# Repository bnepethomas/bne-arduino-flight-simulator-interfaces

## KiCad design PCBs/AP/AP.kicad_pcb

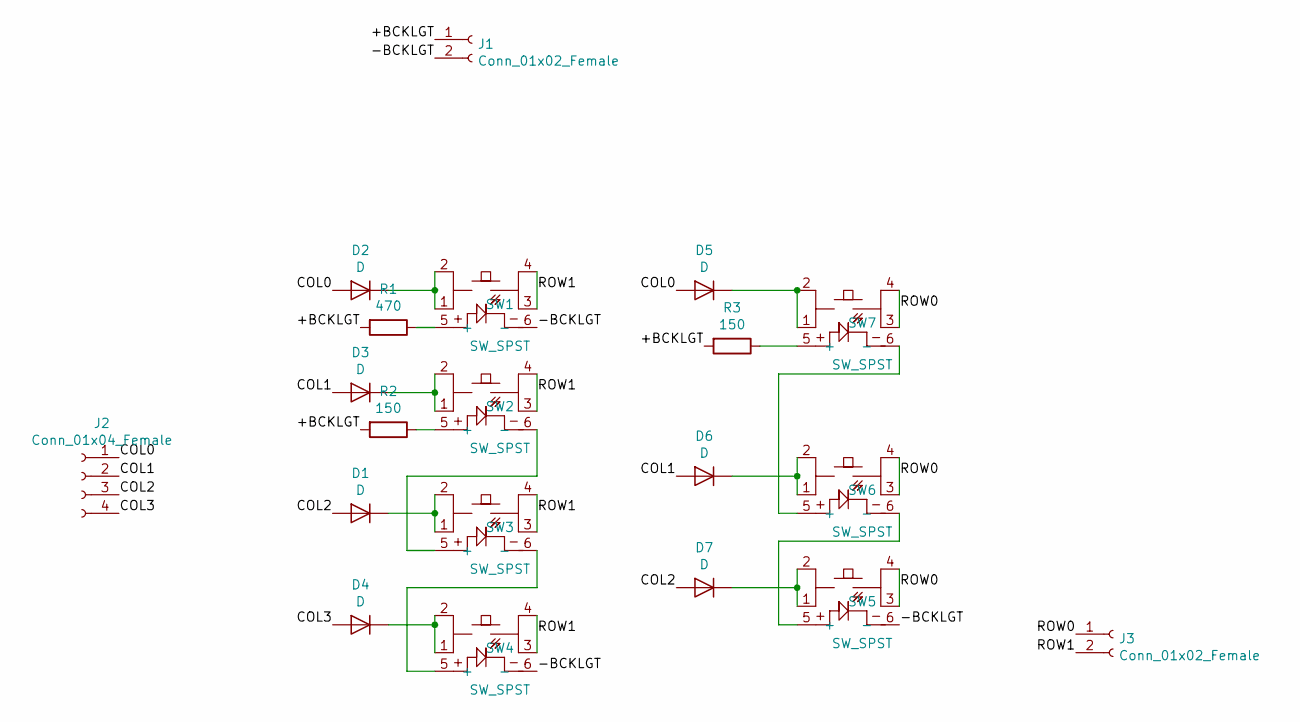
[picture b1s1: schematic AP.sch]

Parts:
D1, D2, D3, D4, D5, D6, D7: D; D_Signal_P7.62mm_Horizontal
J1, J3: Conn_01x02_Female; PinSocket_1x02_P2.54mm_Vertical
J2: Conn_01x04_Female; PinHeader_1x04_P2.54mm_Vertical
R1: 470; R_Axial_DIN0207_L6.3mm_D2.5mm_P7.62mm_Horizontal
R2, R3: 150; R_Axial_DIN0207_L6.3mm_D2.5mm_P7.62mm_Horizontal
SW1, SW2, SW3, SW4, SW5, SW6, SW7: SW_SPST; PT_Small_Tactile_Switch_With_LED

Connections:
/+BCKLGT: J1.1, R1.2, R2.2, R3.2
/-BCKLGT: J1.2, SW1.6 (-), SW4.6 (-), SW5.6 (-)
/COL0: D2.2 (A), D5.2 (A), J2.1
/COL1: D3.2 (A), D6.2 (A), J2.2
/COL2: D1.2 (A), D7.2 (A), J2.3
/COL3: D4.2 (A), J2.4
/ROW0: J3.1, SW5.3, SW5.4, SW6.3, SW6.4, SW7.3, SW7.4
/ROW1: J3.2, SW1.3, SW1.4, SW2.3, SW2.4, SW3.3, SW3.4, SW4.3, SW4.4
unnamed: D1.1 (K), SW3.1, SW3.2
unnamed: D2.1 (K), SW1.1, SW1.2
unnamed: D3.1 (K), SW2.1, SW2.2
unnamed: D4.1 (K), SW4.1, SW4.2
unnamed: D5.1 (K), SW7.1, SW7.2
unnamed: D6.1 (K), SW6.1, SW6.2
unnamed: D7.1 (K), SW5.1, SW5.2
unnamed: R1.1, SW1.5 (+)
unnamed: R2.1, SW2.5 (+)
unnamed: R3.1, SW7.5 (+)
unnamed: SW2.6 (-), SW3.5 (+)
unnamed: SW3.6 (-), SW4.5 (+)
unnamed: SW5.5 (+), SW6.6 (-)
unnamed: SW6.5 (+), SW7.6 (-)

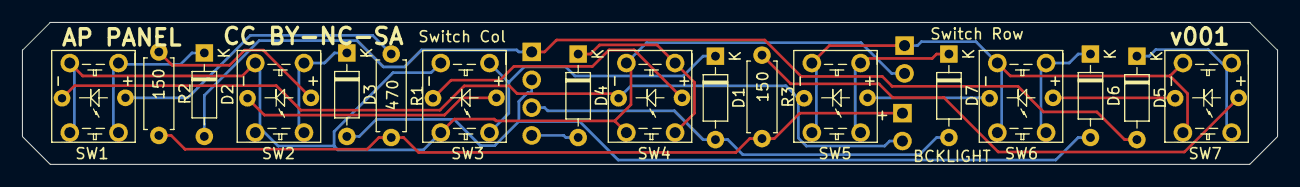
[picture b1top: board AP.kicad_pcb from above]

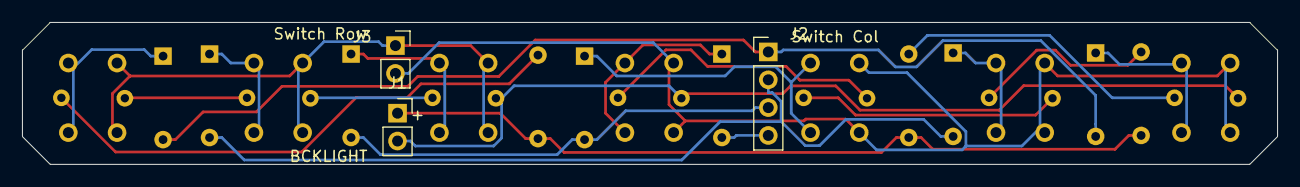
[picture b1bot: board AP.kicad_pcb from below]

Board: 2 copper layers, 114.6 x 13.0 mm, 20 parts (3 on the bottom side), 22 nets.

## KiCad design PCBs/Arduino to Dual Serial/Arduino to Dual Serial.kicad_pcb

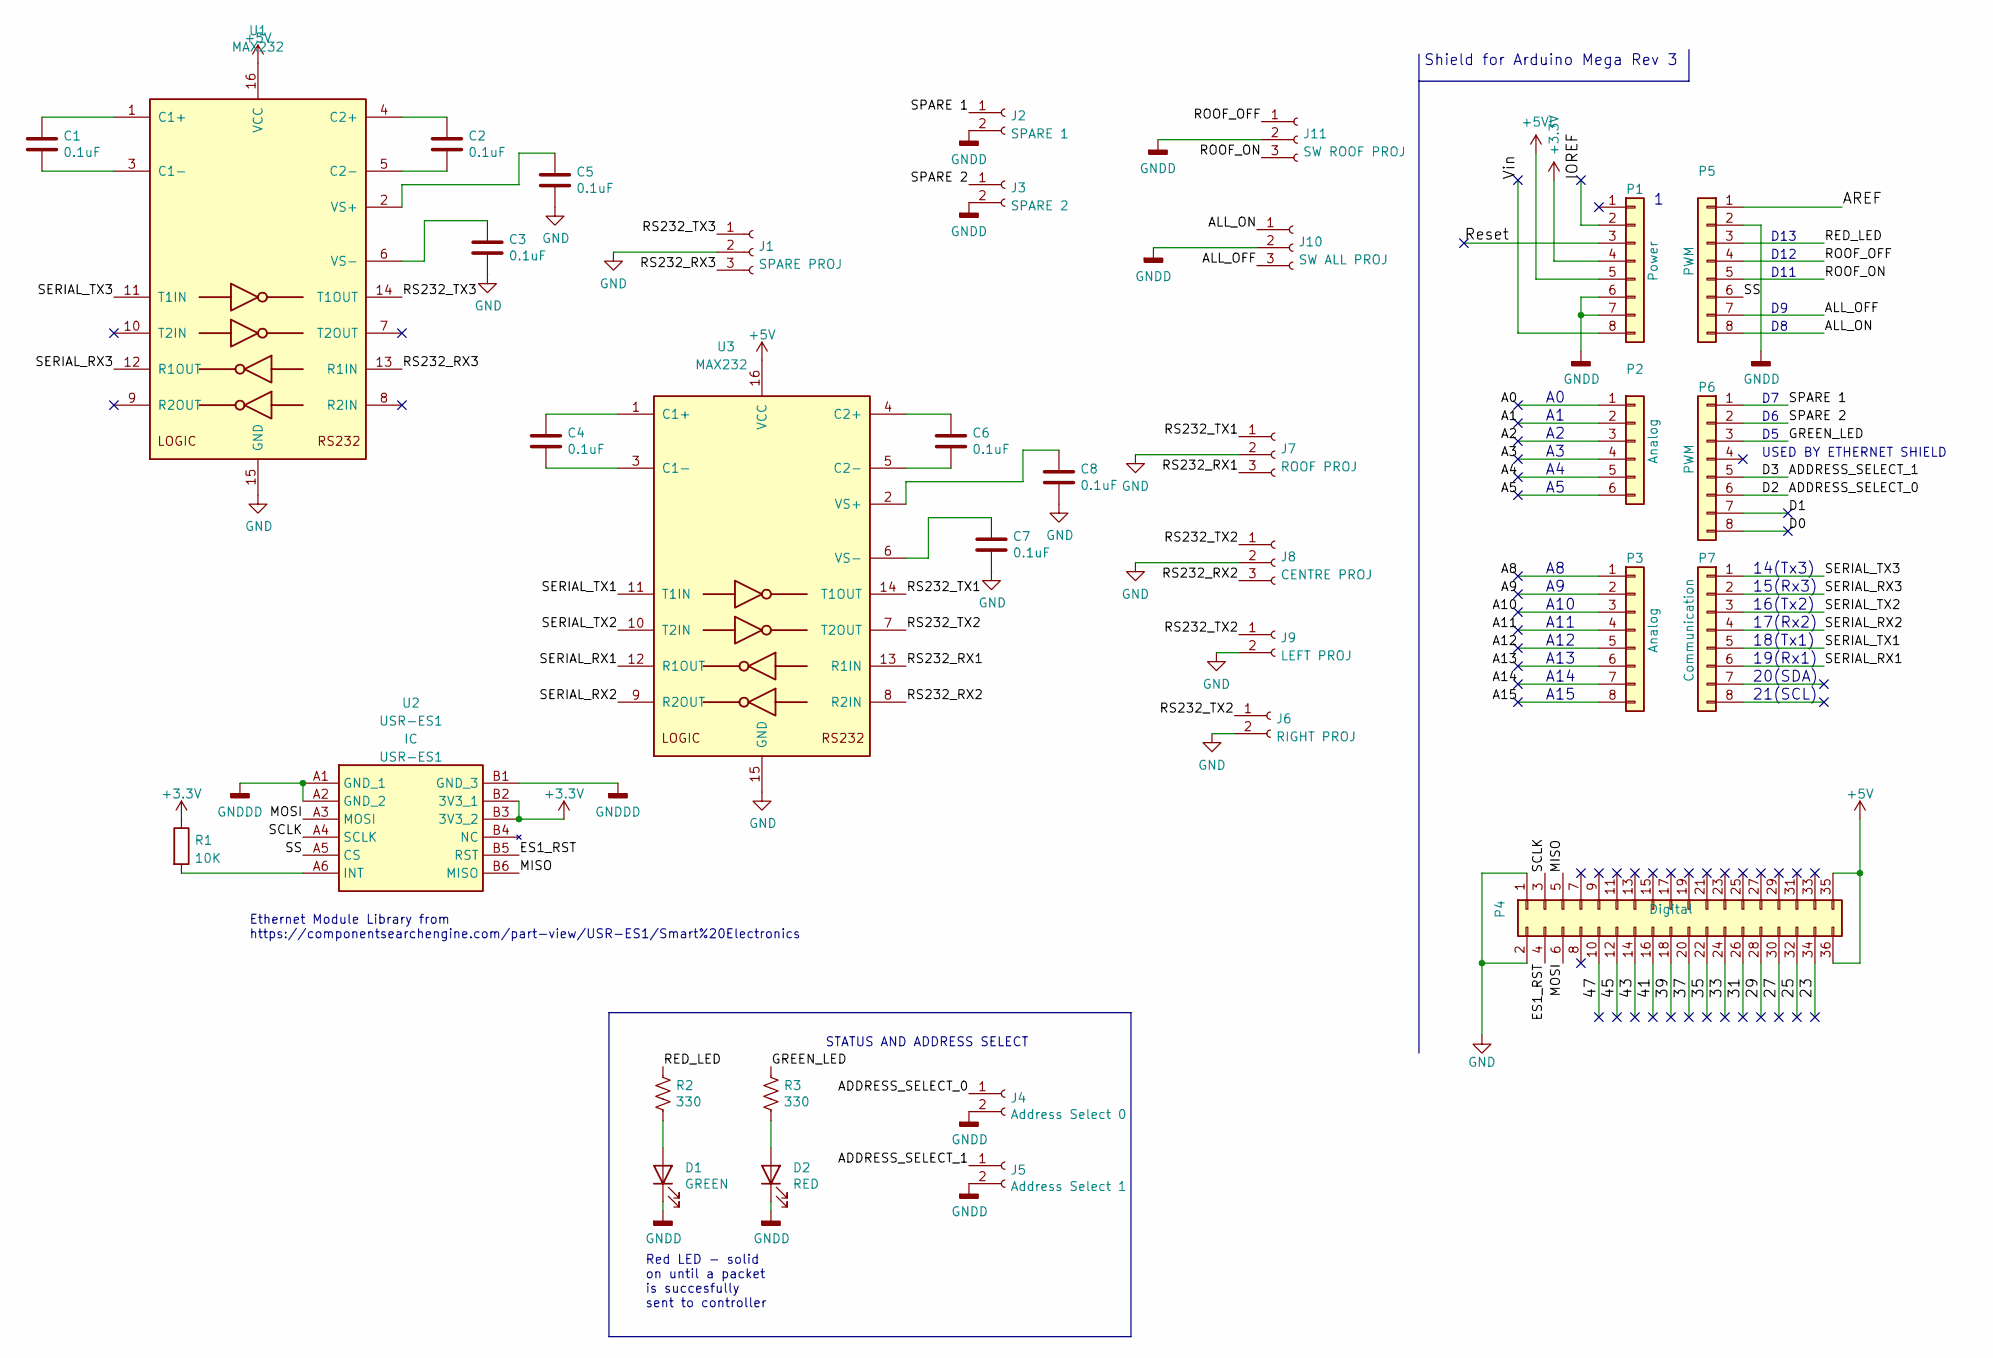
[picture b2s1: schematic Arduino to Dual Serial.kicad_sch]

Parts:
C1, C2, C3, C4, C5, C6, C7, C8: 0.1uF; C_Disc_D4.3mm_W1.9mm_P5.00mm
D1: GREEN; LED_D3.0mm
D2: RED; LED_D3.0mm
J1: SPARE PROJ; Molex_KK-254_AE-6410-03A_1x03_P2.54mm_Vertical
J2: SPARE 1; Molex_KK-254_AE-6410-02A_1x02_P2.54mm_Vertical
J3: SPARE 2; Molex_KK-254_AE-6410-02A_1x02_P2.54mm_Vertical
J4: Address Select 0; PinHeader_1x02_P2.54mm_Vertical
J5: Address Select 1; PinHeader_1x02_P2.54mm_Vertical
J6: RIGHT PROJ; Molex_KK-254_AE-6410-02A_1x02_P2.54mm_Vertical
J7: ROOF PROJ; Molex_KK-254_AE-6410-03A_1x03_P2.54mm_Vertical
J8: CENTRE PROJ; Molex_KK-254_AE-6410-03A_1x03_P2.54mm_Vertical
J9: LEFT PROJ; Molex_KK-254_AE-6410-02A_1x02_P2.54mm_Vertical
J10: SW ALL PROJ; Molex_KK-254_AE-6410-03A_1x03_P2.54mm_Vertical
J11: SW ROOF PROJ; Molex_KK-254_AE-6410-03A_1x03_P2.54mm_Vertical
P1: Power; Socket_Strip_Arduino_1x08
P2: Analog; PinHeader_1x06_P2.54mm_Vertical
P3: Analog; Socket_Strip_Arduino_1x08
P4: Digital; Socket_Strip_Arduino_2x18
P5: PWM; PinHeader_1x08_P2.54mm_Vertical
P6: PWM; Socket_Strip_Arduino_1x08
P7: Communication; Socket_Strip_Arduino_1x08
R1: 10K; PT_R_Axial_DIN0204_L3.6mm_D1.6mm_P2.54mm_Vertical
R2, R3: 330; PT_R_Axial_DIN0204_L3.6mm_D1.6mm_P2.54mm_Vertical
U1, U3: MAX232; DIP-16_W7.62mm
U2: USR-ES1; USRES1; Manufacturer_Part_Number USR-ES1

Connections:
+3.3V: P1.4, R1.1, U2.B2 (3V3_1), U2.B3 (3V3_2)
+5V: P4.35, P4.36, U1.16 (VCC), U3.16 (VCC)
+5VL: P1.5
/23: P4.34
/25: P4.32
/27: P4.30
/29: P4.28
/31: P4.26
/33: P4.24
/35: P4.22
/37: P4.20
/39: P4.18
/41: P4.16
/43: P4.14
/45: P4.12
/47: P4.10
/A0: P2.1
/A1: P2.2
/A2: P2.3
/A3: P2.4
/A4: P2.5
/A5: P2.6
/A8: P3.1
/A9: P3.2
/A10: P3.3
/A11: P3.4
/A12: P3.5
/A13: P3.6
/A14: P3.7
/A15: P3.8
/ADDRESS_SELECT_0: J4.1, P6.6
/ADDRESS_SELECT_1: J5.1, P6.5
/ALL_OFF: J10.3, P5.7
/ALL_ON: J10.1, P5.8
/AREF: P5.1
/D0: P6.8
/D1: P6.7
/ES1_RST: P4.4, U2.B5 (RST)
/GREEN_LED: P6.3, R3.1
/IOREF: P1.2
/MISO: P4.5, U2.B6 (MISO)
/MOSI: P4.6, U2.A3 (MOSI)
/RED_LED: P5.3, R2.1
/ROOF_OFF: J11.1, P5.4
/ROOF_ON: J11.3, P5.5
/RS232_RX1: J7.3, U3.13 (R1IN)
/RS232_RX2: J8.3, U3.8 (R2IN)
/RS232_RX3: J1.3, U1.13 (R1IN)
/RS232_TX1: J7.1, U3.14 (T1OUT)
/RS232_TX2: J6.1, J8.1, J9.1, U3.7 (T2OUT)
/RS232_TX3: J1.1, U1.14 (T1OUT)
/Reset: P1.3
/SCLK: P4.3, U2.A4 (SCLK)
/SERIAL_RX1: P7.6, U3.12 (R1OUT)
/SERIAL_RX2: P7.4, U3.9 (R2OUT)
/SERIAL_RX3: P7.2, U1.12 (R1OUT)
/SERIAL_TX1: P7.5, U3.11 (T1IN)
/SERIAL_TX2: P7.3, U3.10 (T2IN)
/SERIAL_TX3: P7.1, U1.11 (T1IN)
/SPARE 1: J2.1, P6.1
/SPARE 2: J3.1, P6.2
/SS: P5.6, U2.A5 (CS)
/Vin: P1.8
GND: C3.2, C5.2, C7.2, C8.2, J1.2, J6.2, J7.2, J8.2, J9.2, P4.1, P4.2, U1.15 (GND), U3.15 (GND)
unnamed: C1.1, U1.1 (C1+)
unnamed: C1.2, U1.3 (C1-)
unnamed: C2.1, U1.4 (C2+)
unnamed: C2.2, U1.5 (C2-)
unnamed: C3.1, U1.6 (VS-)
unnamed: C4.1, U3.1 (C1+)
unnamed: C4.2, U3.3 (C1-)
unnamed: C5.1, U1.2 (VS+)
unnamed: C6.1, U3.4 (C2+)
unnamed: C6.2, U3.5 (C2-)
unnamed: C7.1, U3.6 (VS-)
unnamed: C8.1, U3.2 (VS+)
unnamed: D1.2 (A), R2.2
unnamed: D2.2 (A), R3.2
unnamed: R1.2, U2.A6 (INT)

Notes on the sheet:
A10
14(Tx3)
21(SCL)
USED BY ETHERNET SHIELD
20(SDA)
A15
A13
17(Rx2)
D12
A11
D13
16(Tx2)
Red LED - solid on until a packet is succesfully sent to controller
18(Tx1)
19(Rx1)
15(Rx3)
D11
Shield for Arduino Mega Rev 3
A14
Ethernet Module Library from https://componentsearchengine.com/part-view/USR-ES1/Smart%20Electronics
STATUS AND ADDRESS SELECT
A12

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
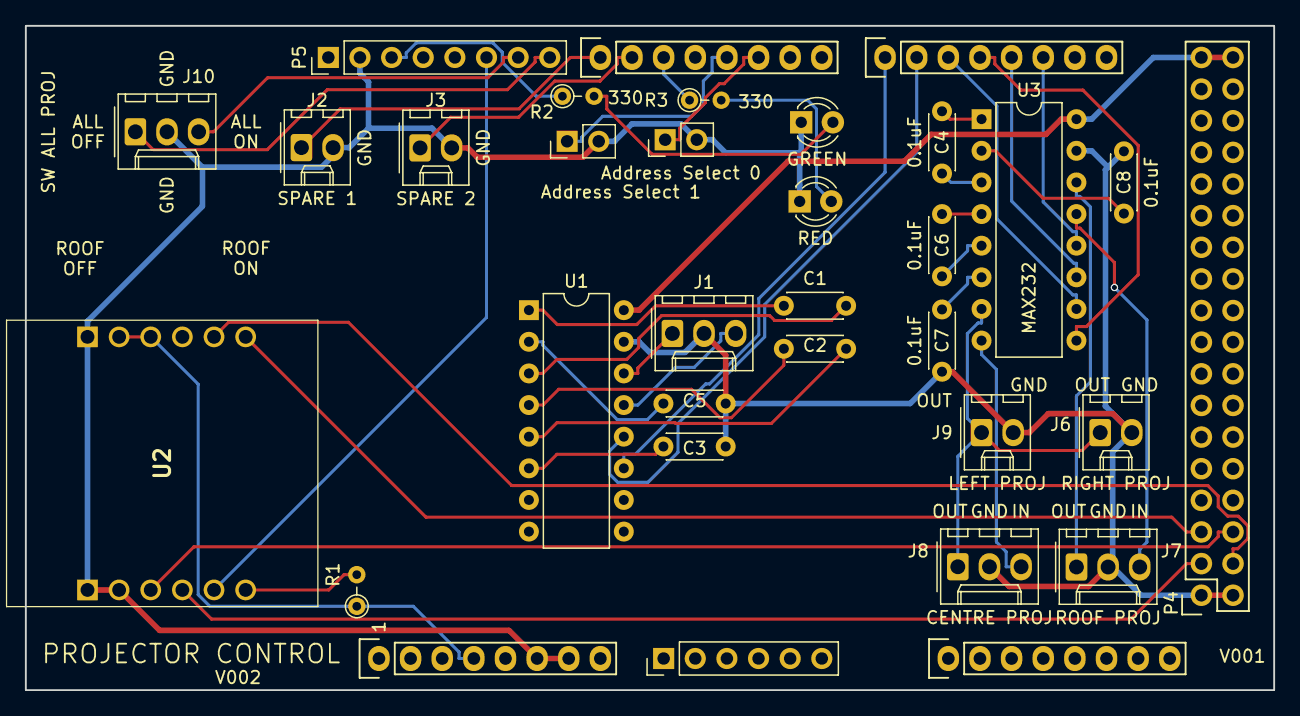
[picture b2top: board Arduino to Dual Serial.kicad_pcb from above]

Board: 2 copper layers, 100.2 x 53.3 mm, 33 parts (0 on the bottom side), 44 nets.

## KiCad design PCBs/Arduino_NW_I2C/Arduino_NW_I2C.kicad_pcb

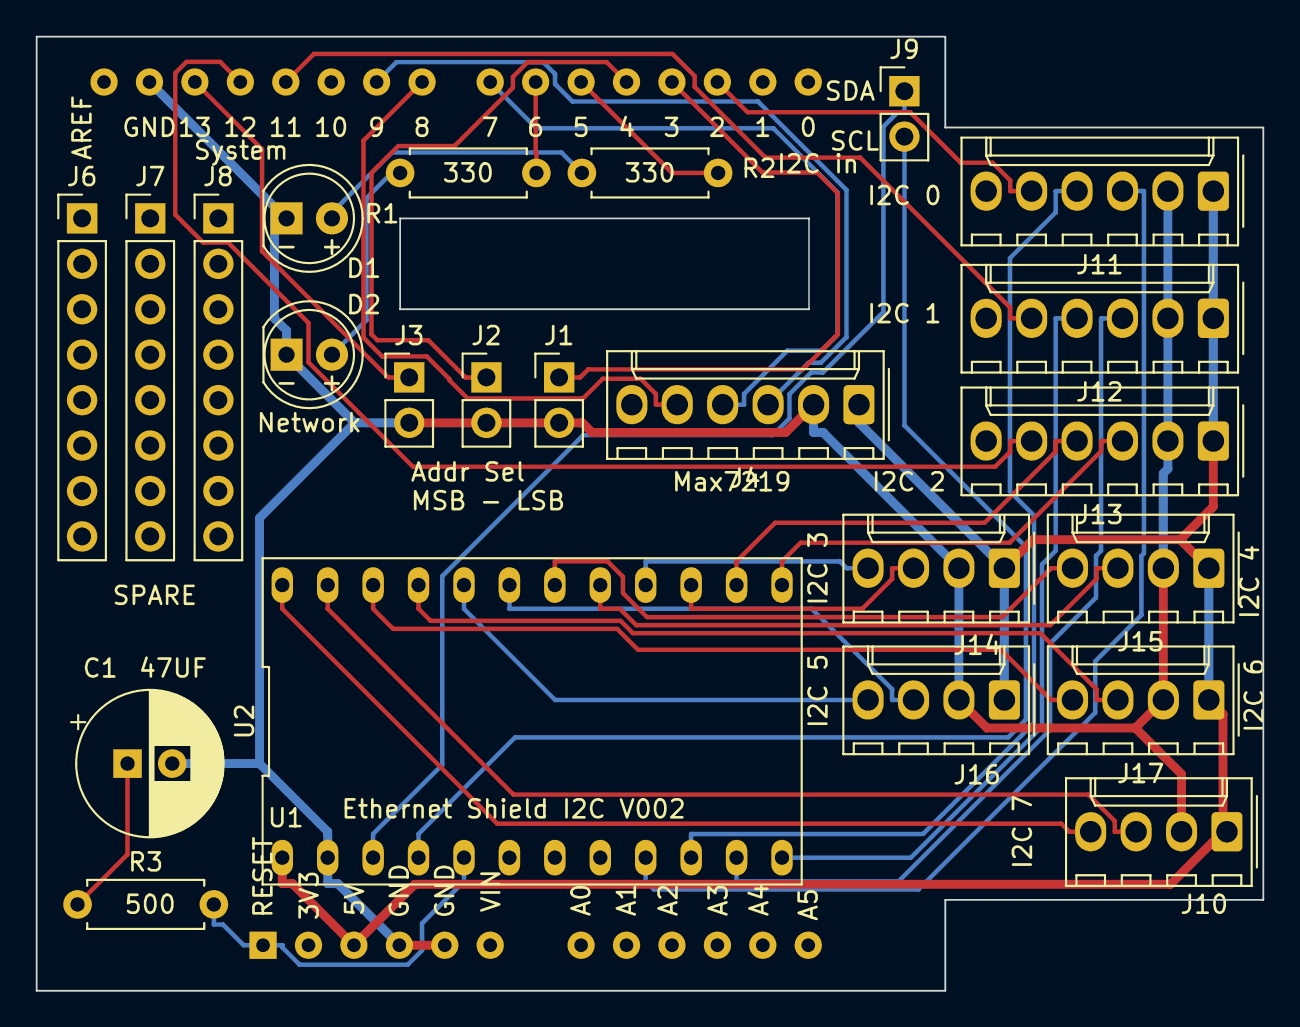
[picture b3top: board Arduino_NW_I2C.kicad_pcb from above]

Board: 2 copper layers, 68.6 x 53.3 mm, 24 parts (0 on the bottom side), 35 nets.

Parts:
C1: 47uF; PT_CP_Radial_D8.0mm_P2.50mm
D1: Green; LED_D5.0mm
D2: Red; LED_D5.0mm
J1: A0; PinHeader_1x02_P2.54mm_Vertical
J2: A1; PinHeader_1x02_P2.54mm_Vertical
J3: A2; PinHeader_1x02_P2.54mm_Vertical
J4, J11, J12: PT_Conn_01x06; Molex_1x06_P2.54mm_Vertical
J6, J7, J8: Conn_01x08_Female; PinHeader_1x08_P2.54mm_Vertical
J9: Conn_01x02_Female; PinHeader_1x02_P2.54mm_Vertical
J10, J14, J15, J16, J17: PT_Conn_01x04; Molex_1x04_P2.54mm_Vertical
J13: PT_Conn_01x04; Molex_1x06_P2.54mm_Vertical
R1, R2: 330; R_Axial_DIN0207_L6.3mm_D2.5mm_P7.62mm_Horizontal
R3: 500; R_Axial_DIN0207_L6.3mm_D2.5mm_P7.62mm_Horizontal
U1: PT_Ethernet_Shield; PT_Ethernet_Shield_v001
U2: MUX; Adafruit_TCA9548A

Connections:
+5V: J4.1, J10.1, J11.1, J12.1, J13.1, J14.1, J15.1, J16.1, J17.1, U1.3, U2.+5V
/RST_1: J11.5, U1.15
/RST_2: J12.5, U1.24
/RST_3: J13.5, U1.25
/SC0: J11.3, U2.SC0
/SC1: J12.3, U2.SC1
/SC2: J13.3, U2.SC2
/SC3: J14.3, U2.SC3
/SC4: J15.3, U2.SC4
/SC5: J16.3, U2.SC5
/SC6: J17.3, U2.SC6
/SC7: J10.3, U2.SC7
/SD0: J11.4, U2.SD0
/SD1: J12.4, U2.SD1
/SD2: J13.4, U2.SD2
/SD3: J14.4, U2.SD3
/SD4: J15.4, U2.SD4
/SD5: J16.4, U2.SD5
/SD6: J17.4, U2.SD6
/SD7: J10.4, U2.SD7
GND: C1.2, D1.1, D2.1, J1.2, J2.2, J3.2, J4.2, J10.2, J11.2, J12.2, J13.2, J14.2, J15.2, J16.2, J17.2, U1.4, U1.5, U1.27, U2.GND
unnamed: C1.1, R3.1
unnamed: D1.2, R2.1
unnamed: D2.2, R1.1
unnamed: J1.1, U1.16
unnamed: J2.1, U1.17
unnamed: J3.1, U1.26
unnamed: J4.3, U1.22
unnamed: J4.4, U1.20
unnamed: J4.5, U1.21
unnamed: J9.1, U2.SDA
unnamed: J9.2, U2.SCL
unnamed: R1.2, U1.19
unnamed: R2.2, U1.18
unnamed: R3.2, U1.1, U2.RST

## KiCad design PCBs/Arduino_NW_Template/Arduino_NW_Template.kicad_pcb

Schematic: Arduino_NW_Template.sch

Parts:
C1: CP1; PT_CP_Radial_D8.0mm_P2.50mm
C2, C3, C4, C5, C6, C7, C8, C9, C10, C11, C12, C13, C14, C15: C; C_Disc_D4.3mm_W1.9mm_P5.00mm
D1, D2: LED; LED_D5.0mm
J1, J2, J3: Conn_01x02_Female; PinHeader_1x02_P2.54mm_Vertical
J4, J5, J12, J13: PT_Conn_01x06; PT_PinHeader_1x06_P2.54mm_Vertical
J6, J7, J8: Conn_01x08_Female; PinHeader_1x08_P2.54mm_Vertical
J9, J11: Conn_01x04_Female; PinHeader_1x04_P2.54mm_Vertical
J10: Conn_01x08_Female; PT_PinHeader_1x08_P2.54mm_Vertical
R1, R2, R3: R; PT_R_Axial_DIN0204_L3.6mm_D1.6mm_P2.54mm_Vertical
U1: PT_Ethernet_Shield; PT_Ethernet_Shield_v001

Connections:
+5V: J4.1, J5.1, J10.1, J12.1, J13.1, U1.3 (5V)
GND: C1.2, C2.2, C3.2, C4.2, C5.2, C6.2, C7.2, C8.2, C9.2, C10.2, C11.2, C12.2, C13.2, C14.2, C15.2, D1.1, D2.1, J1.1, J2.1, J3.1, J4.2, J5.2, J10.2, J12.2, J13.2, U1.4 (GND), U1.5 (GND), U1.27 (GND)
unnamed: C1.1, R3.1
unnamed: C2.1, J10.3, U1.7 (A0)
unnamed: C3.1, J10.4, U1.8 (A1)
unnamed: C4.1, J10.5, U1.9 (A2)
unnamed: C5.1, J10.6, U1.10 (A3)
unnamed: C6.1, J10.7, U1.11 (A4)
unnamed: C7.1, J10.8, U1.12 (A5)
unnamed: C8.1, J9.1, J12.3
unnamed: C9.1, J9.2, J12.4
unnamed: C10.1, J11.1, J13.3
unnamed: C11.1, J9.3, J12.5
unnamed: C12.1, J11.2, J13.4
unnamed: C13.1, J9.4, J12.6
unnamed: C14.1, J11.3, J13.5
unnamed: C15.1, J11.4, J13.6
unnamed: D1.2, R2.1
unnamed: D2.2, R1.1
unnamed: J1.2, U1.15 (D2)
unnamed: J2.2, U1.16 (D3)
unnamed: J4.3, U1.22 (D9)
unnamed: J4.4, U1.20 (D7)
unnamed: J4.5, U1.21 (D8)
unnamed: J5.4, U1.24 (D11)
unnamed: J5.5, U1.25 (D12)
unnamed: J5.6, U1.26 (D13)
unnamed: R1.2, U1.19 (D6)
unnamed: R2.2, U1.18 (D5)
unnamed: R3.2, U1.1 (RESET)

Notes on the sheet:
Address Select (0-7)
Cannot use D4 and D10 as they are used by the Ethernet shield

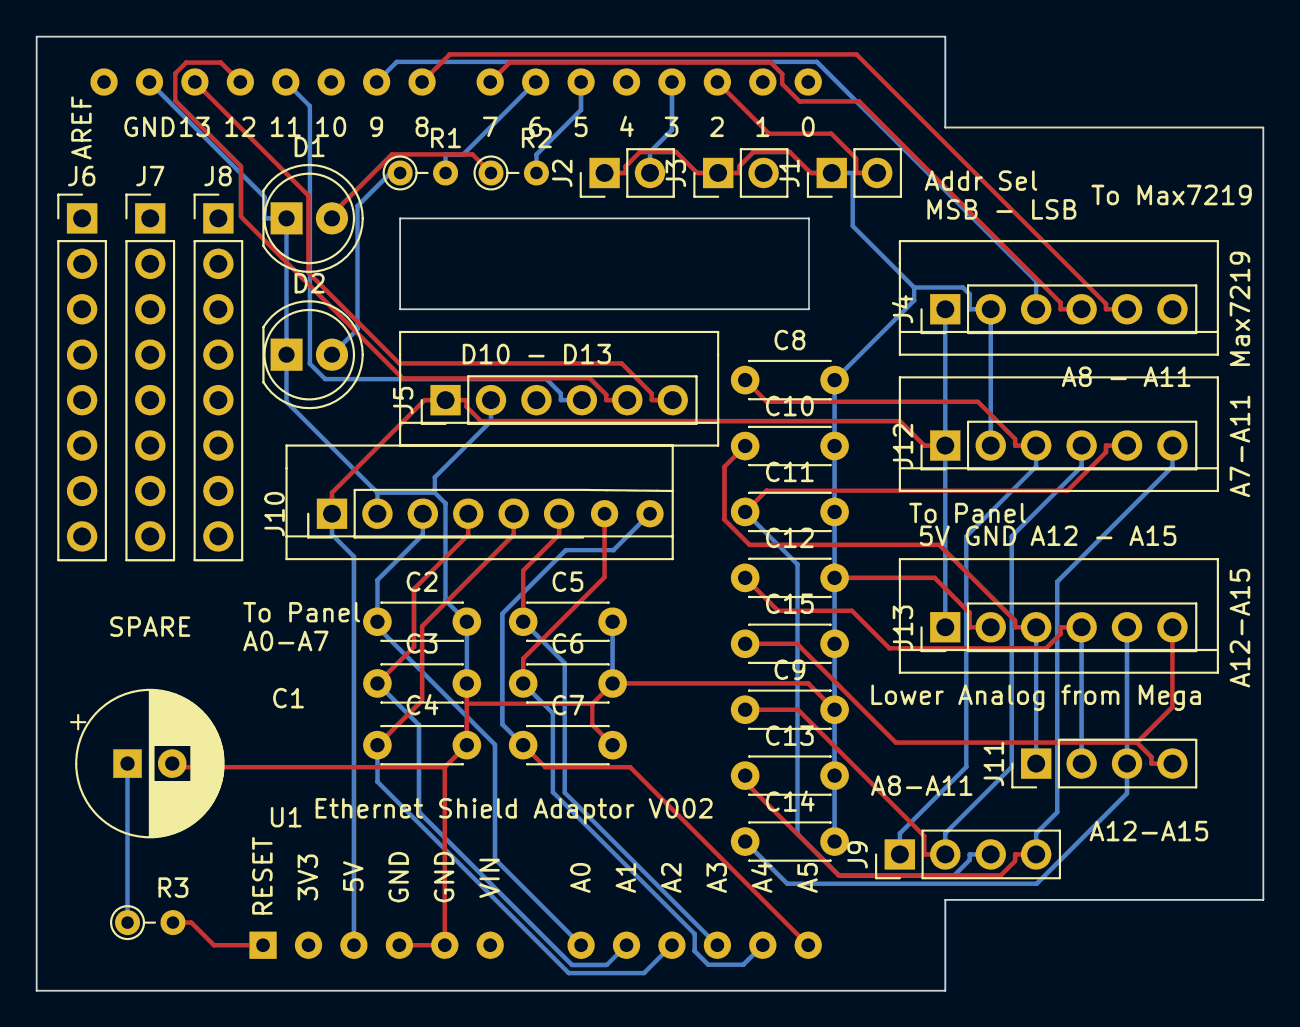
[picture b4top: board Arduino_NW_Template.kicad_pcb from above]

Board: 2 copper layers, 68.6 x 53.3 mm, 34 parts (0 on the bottom side), 30 nets.

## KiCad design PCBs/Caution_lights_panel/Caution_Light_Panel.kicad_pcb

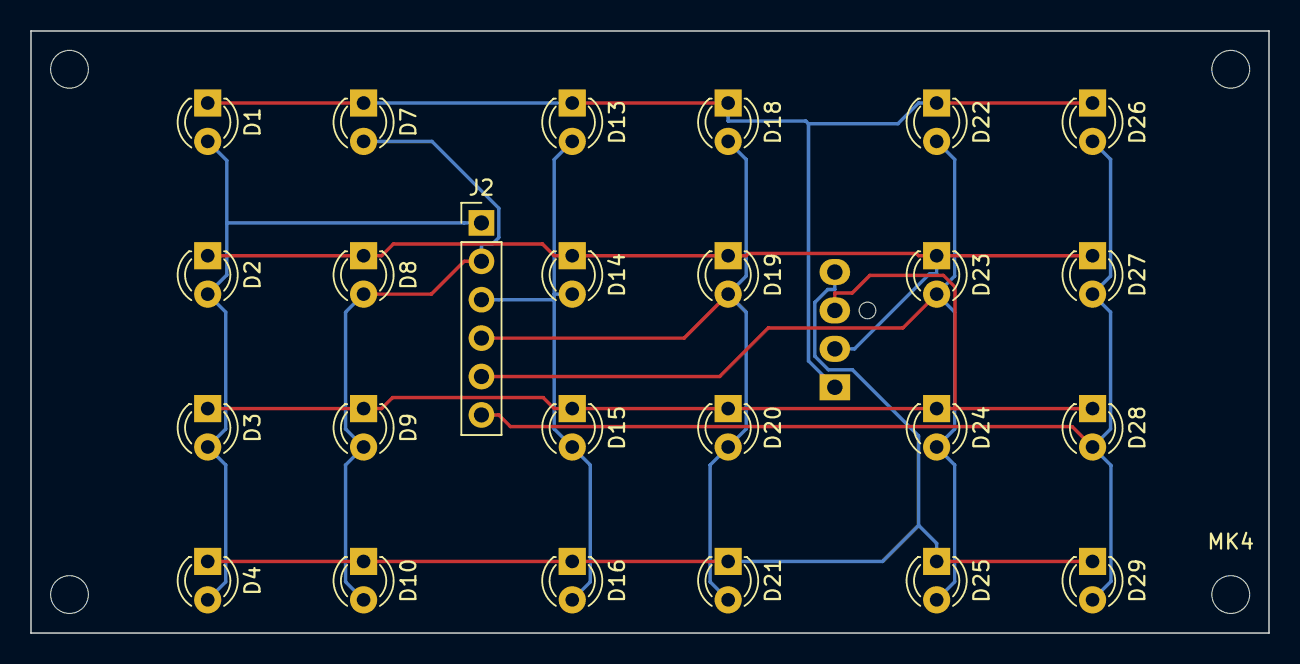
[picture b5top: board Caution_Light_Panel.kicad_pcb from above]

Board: 2 copper layers, 81.9 x 39.8 mm, 30 parts (1 on the bottom side), 10 nets.

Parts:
D1: 0,0; LED_D3.0mm_FlatTop
D2: 1,0; LED_D3.0mm_FlatTop
D3: 2,0; LED_D3.0mm_FlatTop
D4: 3,0; LED_D3.0mm_FlatTop
D7: 0,1; LED_D3.0mm_FlatTop
D8: 1,1; LED_D3.0mm_FlatTop
D9: 2,1; LED_D3.0mm_FlatTop
D10: 3,1; LED_D3.0mm_FlatTop
D13: 0,2; LED_D3.0mm_FlatTop
D14: 1,2; LED_D3.0mm_FlatTop
D15: 2,2; LED_D3.0mm_FlatTop
D16: 3,2; LED_D3.0mm_FlatTop
D18: 0,3; LED_D3.0mm_FlatTop
D19: 1.3; LED_D3.0mm_FlatTop
D20: 2,3; LED_D3.0mm_FlatTop
D21: 3,3; LED_D3.0mm_FlatTop
D22: 0.4; LED_D3.0mm_FlatTop
D23: 1.4; LED_D3.0mm_FlatTop
D24: 2,4; LED_D3.0mm_FlatTop
D25: 3,4; LED_D3.0mm_FlatTop
D26: 0.5; LED_D3.0mm_FlatTop
D27: 1.5; LED_D3.0mm_FlatTop
D28: 2,5; LED_D3.0mm_FlatTop
D29: 3,5; LED_D3.0mm_FlatTop
J1: PWR; FanPinHeader_1x04_P2.54mm_Vertical
J2: PWR; PinHeader_1x06_P2.54mm_Vertical
MK1, MK2, MK3, MK4: Mounting_Hole; MountingHole_2.5mm

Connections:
/Dig0: D1.1, D7.1, D13.1, D18.1, D22.1, D26.1, J1.1
/Dig1: D2.1, D8.1, D14.1, D19.1, D23.1, D27.1, J1.2
/Dig2: D3.1, D9.1, D15.1, D20.1, D24.1, D28.1, J1.3
/Dig3: D4.1, D10.1, D16.1, D21.1, D25.1, D29.1, J1.4
/SegA: D7.2, D8.2, D9.2, D10.2, J2.2
/SegB: D13.2, D14.2, D15.2, D16.2, J2.3
/SegC: D18.2, D19.2, D20.2, D21.2, J2.4
/SegD: D22.2, D23.2, D24.2, D25.2, J2.5
/SegDP: D1.2, D2.2, D3.2, D4.2, J2.1
/SegE: D26.2, D27.2, D28.2, D29.2, J2.6

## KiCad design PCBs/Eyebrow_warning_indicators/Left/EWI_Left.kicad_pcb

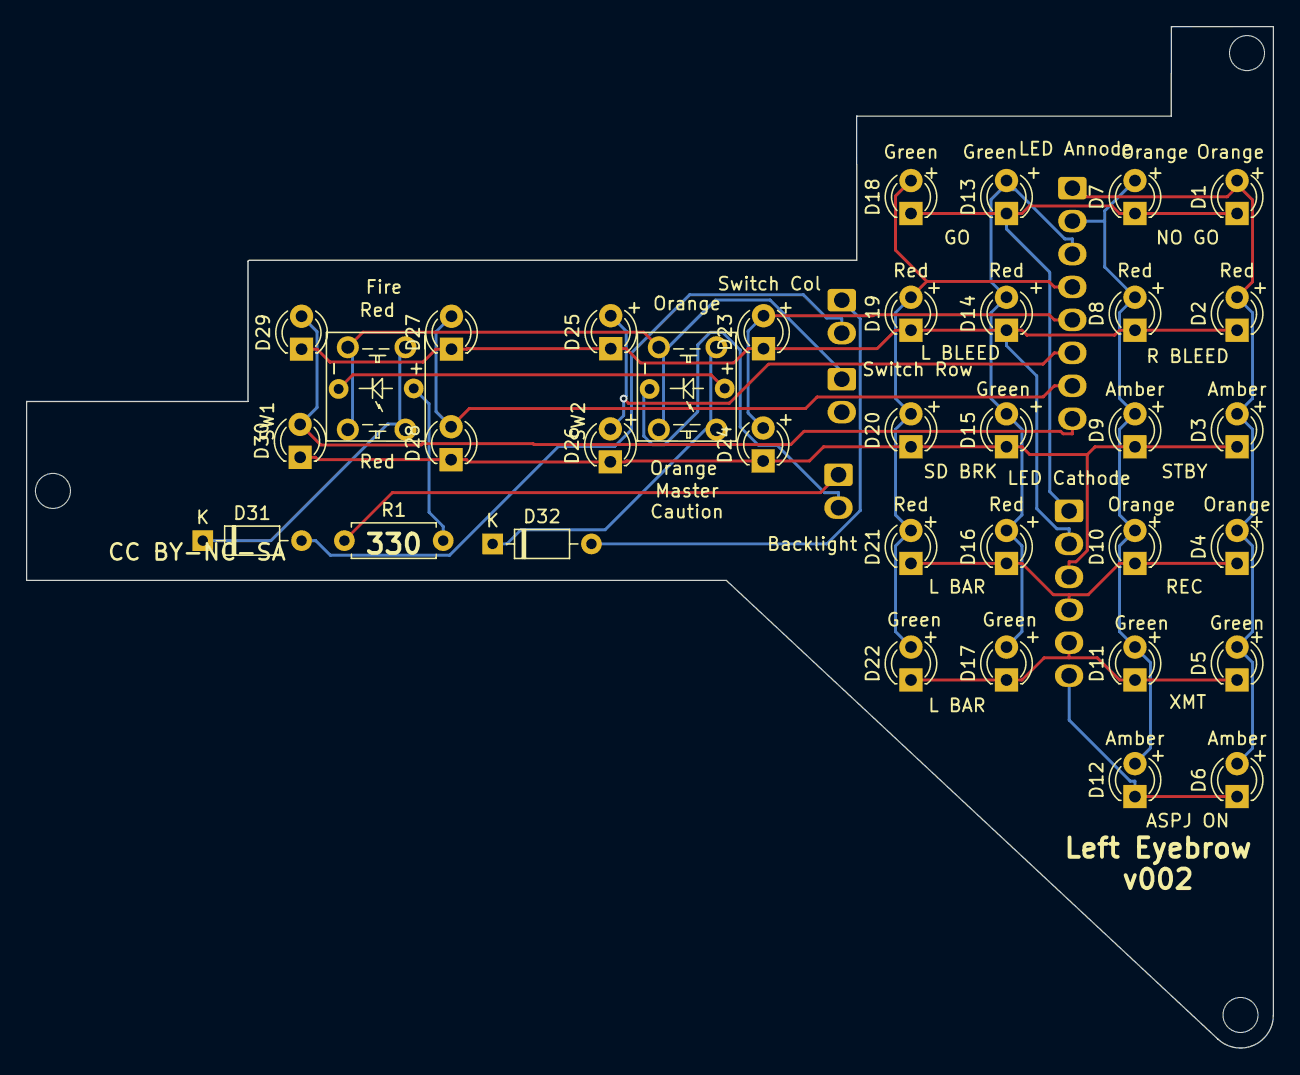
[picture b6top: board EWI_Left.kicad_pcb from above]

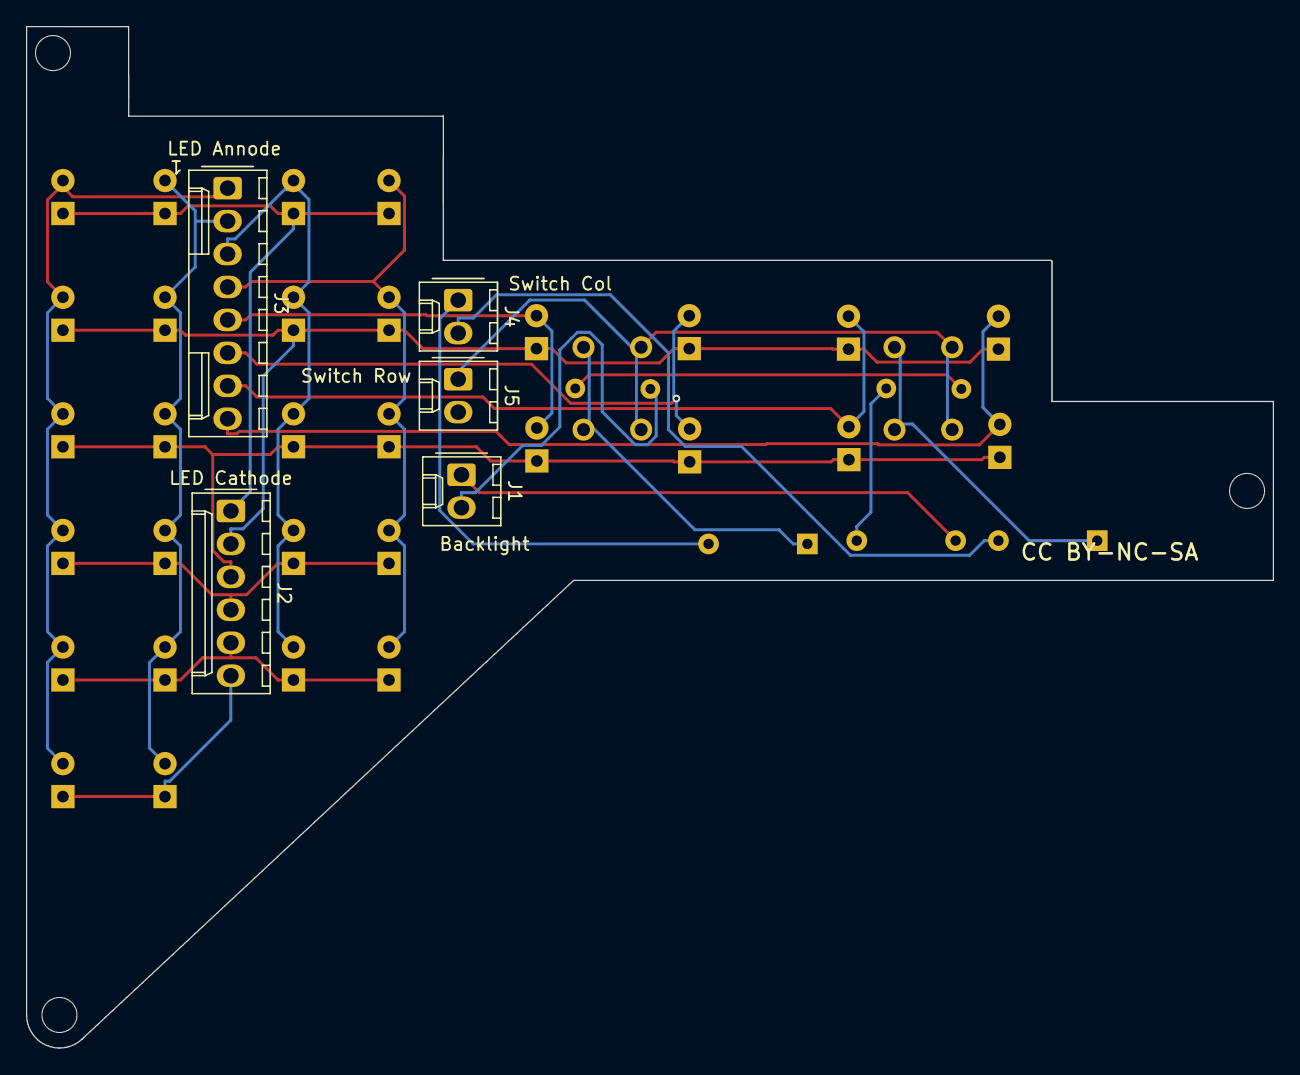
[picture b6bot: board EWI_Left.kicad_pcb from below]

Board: 2 copper layers, 96.1 x 78.8 mm, 43 parts (5 on the bottom side), 23 nets.

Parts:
D1: 0,0; LED_D3.0mm_FlatTop
D2: 1,0; LED_D3.0mm_FlatTop
D3: 2,0; LED_D3.0mm_FlatTop
D4: 3,0; LED_D3.0mm_FlatTop
D5: 4,0; LED_D3.0mm_FlatTop
D6: 5,0; LED_D3.0mm_FlatTop
D7: 0,1; LED_D3.0mm_FlatTop
D8: 1,1; LED_D3.0mm_FlatTop
D9: 2,1; LED_D3.0mm_FlatTop
D10: 3,1; LED_D3.0mm_FlatTop
D11: 4,1; LED_D3.0mm_FlatTop
D12: 5,1; LED_D3.0mm_FlatTop
D13: 0,2; LED_D3.0mm_FlatTop
D14: 1,2; LED_D3.0mm_FlatTop
D15: 2,2; LED_D3.0mm_FlatTop
D16: 3,2; LED_D3.0mm_FlatTop
D17: 4,2; LED_D3.0mm_FlatTop
D18: 0,3; LED_D3.0mm_FlatTop
D19: 1.3; LED_D3.0mm_FlatTop
D20: 2,3; LED_D3.0mm_FlatTop
D21: 3,3; LED_D3.0mm_FlatTop
D22: 4,3; LED_D3.0mm_FlatTop
D23: 1.4; LED_D3.0mm_FlatTop
D24: 2,4; LED_D3.0mm_FlatTop
D25: 1.5; LED_D3.0mm_FlatTop
D26: 2,5; LED_D3.0mm_FlatTop
D27: 1.6; LED_D3.0mm_FlatTop
D28: 2,6; LED_D3.0mm_FlatTop
D29: 1.7; LED_D3.0mm_FlatTop
D30: 2,7; LED_D3.0mm_FlatTop
D31, D32: D; D_Signal_P7.62mm_Horizontal
J1: Backlight; Molex_1x02_P2.54mm_Vertical
J2: Led Cathode; Molex_1x06_P2.54mm_Vertical
J3: Led Annode; Molex_1x08_P2.54mm_Vertical
J4: SwitchCol; Molex_1x02_P2.54mm_Vertical
J5: SwitchRow; Molex_1x02_P2.54mm_Vertical
MK1, MK2, MK3: Mounting_Hole; MountingHole_2.7mm_M2.5_ISO14580
R1: 330; R_Axial_DIN0207_L6.3mm_D2.5mm_P7.62mm_Horizontal
SW1: IN SWTCH; PT_Small_Tactile_Switch_With_LED
SW2: OUT SWTCH; PT_Small_Tactile_Switch_With_LED

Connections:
/Dig0: D1.1, D7.1, D13.1, D18.1, J2.1
/Dig1: D2.1, D8.1, D14.1, D19.1, D23.1, D25.1, D27.1, D29.1, J2.2
/Dig2: D3.1, D9.1, D15.1, D20.1, D24.1, D26.1, D28.1, D30.1, J2.3
/Dig3: D4.1, D10.1, D16.1, D21.1, J2.4
/Dig4: D5.1, D11.1, D17.1, D22.1, J2.5
/Dig5: D6.1, D12.1, J2.6
/SegA: D7.2, D8.2, D9.2, D10.2, D11.2, D12.2, J3.2
/SegB: D13.2, D14.2, D15.2, D16.2, D17.2, J3.3
/SegC: D18.2, D19.2, D20.2, D21.2, D22.2, J3.4
/SegD: D23.2, D24.2, J3.5
/SegDP: D1.2, D2.2, D3.2, D4.2, D5.2, D6.2, J3.1
/SegE: D25.2, D26.2, J3.6
/SegF: D27.2, D28.2, J3.7
/SegG: D29.2, D30.2, J3.8
unnamed: D31.1, SW1.1, SW1.2
unnamed: D31.2, J4.2
unnamed: D32.1, SW2.1, SW2.2
unnamed: D32.2, J4.1
unnamed: J1.1, R1.1
unnamed: J1.2, SW2.6
unnamed: J5.1, SW1.3, SW1.4, SW2.3, SW2.4
unnamed: R1.2, SW1.5
unnamed: SW1.6, SW2.5

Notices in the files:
PCBs/AP/AP.kicad_pcb:
CC BY-NC-SA
